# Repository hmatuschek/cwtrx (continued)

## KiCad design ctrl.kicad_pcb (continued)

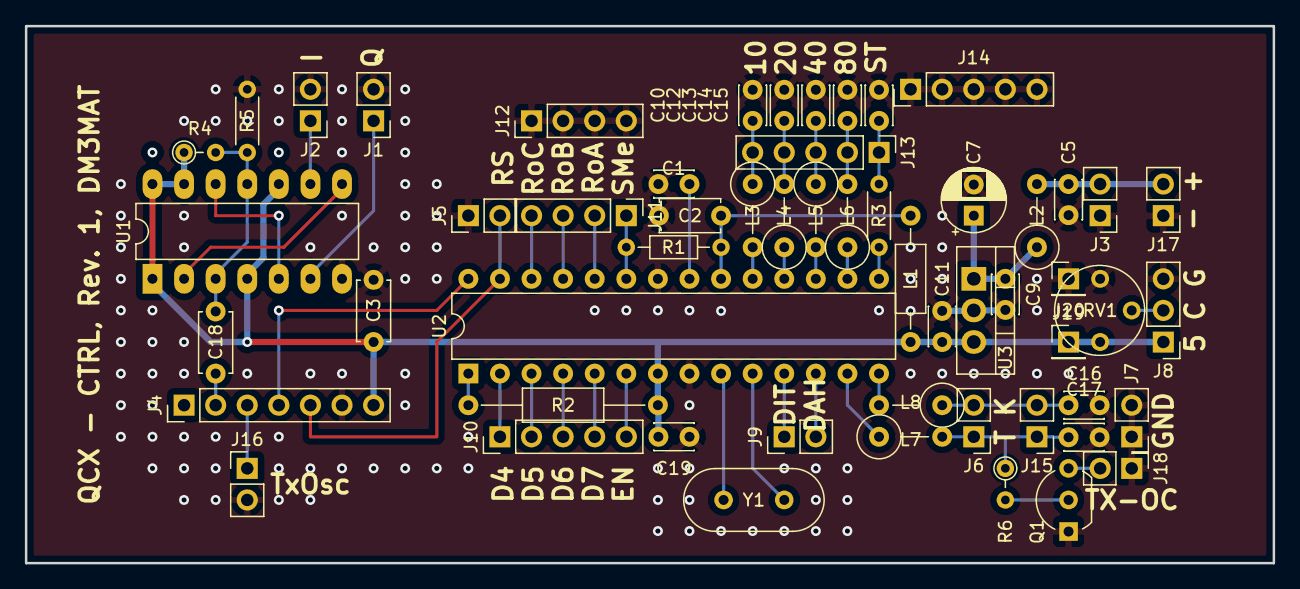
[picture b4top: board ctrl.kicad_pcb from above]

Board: 2 copper layers, 100.3 x 43.2 mm, 56 parts (0 on the bottom side), 46 nets.

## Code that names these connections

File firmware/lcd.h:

// Ansteuerung eines HD44780 kompatiblen LCD im 4-Bit-Interfacemodus
// http://www.mikrocontroller.net/articles/AVR-GCC-Tutorial/LCD-Ansteuerung
//

#ifndef __LCD_H__
#define __LCD_H__

#include <avr/io.h>
#include <stdint.h>

// Data port, DDR and pins
#define LCDD_PORT  PORTD
#define LCDD_DDR   DDRD
#define LCD_DB     PD0
// Reset port, DDR and pin
#define LCDR_PORT  PORTC
#define LCDR_DDR   DDRC
#define LCD_RS     PC4
// Chipselect port, DDR and pin
#define LCDE_PORT  PORTD
#define LCDE_DDR   DDRD
#define LCD_EN     PD4


/* Initialisierung: muss ganz am Anfang des Programms aufgerufen werden. */
void lcd_init(void);

/* LCD löschen */
void lcd_clear(void);

/* Cursor in die 1. Zeile, 0-te Spalte */
void lcd_home(void);

/* Cursor an eine beliebige Position */
void lcd_setcursor(uint8_t spalte, uint8_t zeile);
void lcd_showcursor();
void lcd_blinkcursor();
void lcd_hidecursor();

/* Ausgabe eines einzelnen Zeichens an der aktuellen Cursorposition */
void lcd_data(uint8_t data);

/* Ausgabe eines Strings an der aktuellen Cursorposition */
void lcd_string(const char *data);

/* Print frequency in Hz */
void lcd_freq(uint32_t freq);

void lcd_print_uint16(uint16_t value, uint8_t width);
void lcd_print_pllcorr(int32_t value);
void lcd_print_int32(int32_t value, uint8_t width);

/* Definition eines benutzerdefinierten Sonderzeichens.
 * data muss auf ein Array[8] mit den Zeilencodes des zu definierenden Zeichens
 * zeigen. Später können diese mit lcd_data(0-7) aufgerufen werden */
void lcd_generatechar(uint8_t addr, const uint8_t *data);

/* Ausgabe eines Kommandos an das LCD. */
void lcd_command(uint8_t data);


#endif // __LCD_H__

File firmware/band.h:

#ifndef __BAND_H__
#define __BAND_H__

#include <avr/io.h>

#define BAND_80_60_PORT          PORTB
#define BAND_80_60_DDR           DDRB
#define BAND_80_60_BIT           PB0
#define BAND_40_30_PORT       PORTD
#define BAND_40_30_DDR        DDRD
#define BAND_40_30_BIT        PD7
#define BAND_20_17_PORT       PORTD
#define BAND_20_17_DDR        DDRD
#define BAND_20_17_BIT        PD6
#define BAND_15_12_10_PORT PORTD
#define BAND_15_12_10_DDR  DDRD
#define BAND_15_12_10_BIT  PD5

typedef enum {
  BAND_80 = 0,
  BAND_60,
  BAND_40,
  BAND_30,
  BAND_20,
  BAND_17,
  BAND_15,
  BAND_12,
  BAND_10
} Band;

void band_init();
void band_set(Band band);

#endif // __BAND_H__

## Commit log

2019-05-09 Init.
2019-05-10 Backup.
2019-07-22 Fixed minors.
2019-11-17 Added libs and fixed footprints.
2019-11-17 Updated library.
2020-02-01 Minor fixes
2020-03-03 Fixed CW keyer (J).
2020-03-26 Fixed firmware.
2020-04-28 Fixed greet text editor.
2020-05-15 Backup for rev. 2
2020-05-15 Added revision 2 hardware.
2020-05-15 Added missing sub-circuits.
2020-05-17 backup rev. 2
2020-06-09 Fixed greeing editor.
2020-06-13 Minor fixes to LP filter.
2020-06-13 Added mechanical BOM
2020-06-13 Added Reicheld CSV.
2020-06-14 Implemented factory reset & EncType
2020-06-14 Removed EEPROM RefCorr value.
2020-06-14 Fixed tuning noises.
2020-06-17 Fixed minor issues.
2020-06-17 fixed BOM.
2020-06-23 Added quick-set.
2020-06-23 Fixed enc. type setting.
2020-06-23 Fixed RX/TX sw. on PA.
2020-06-23 Fixed manual-
2020-06-23 Fixed rot enc.
2020-06-24 Fixed docs.
2020-06-24 Fixed PA.
2020-06-27 Fixed menu.
2020-07-23 Started german manual.
2020-07-23 Ext. Baumappe.
2020-07-23 Completed Baumappe.
2020-07-25 Fixed manual.
2020-07-25 Fixed Baumappe.
2020-08-26 Added interactive bom
2020-08-30 Fixed manuals.
2020-08-30 Oops.
2021-01-26 Fixed BOM
2021-02-06 Fixed german manual.
2021-03-09 Added drill-plan for back side.
2021-06-17 Fixed keyer 'z'.
2021-12-05 Implemented iambic mode B.
2021-12-05 Implemented paddle reversal.
2021-12-05 Fixed keyer type menu.
2021-12-21 Implemented iambic latch.
2021-12-25 Basically reimplemented the keyer.
2021-12-25 Cleanup.
2021-12-26 Prep release of firmware version 2.5.
2021-12-27 Fixed auto-text and automatic key detection.
2025-08-13 Cleanup of FW.
2025-08-13 Fixed auto keyer.
2025-08-13 Added SoC display.
